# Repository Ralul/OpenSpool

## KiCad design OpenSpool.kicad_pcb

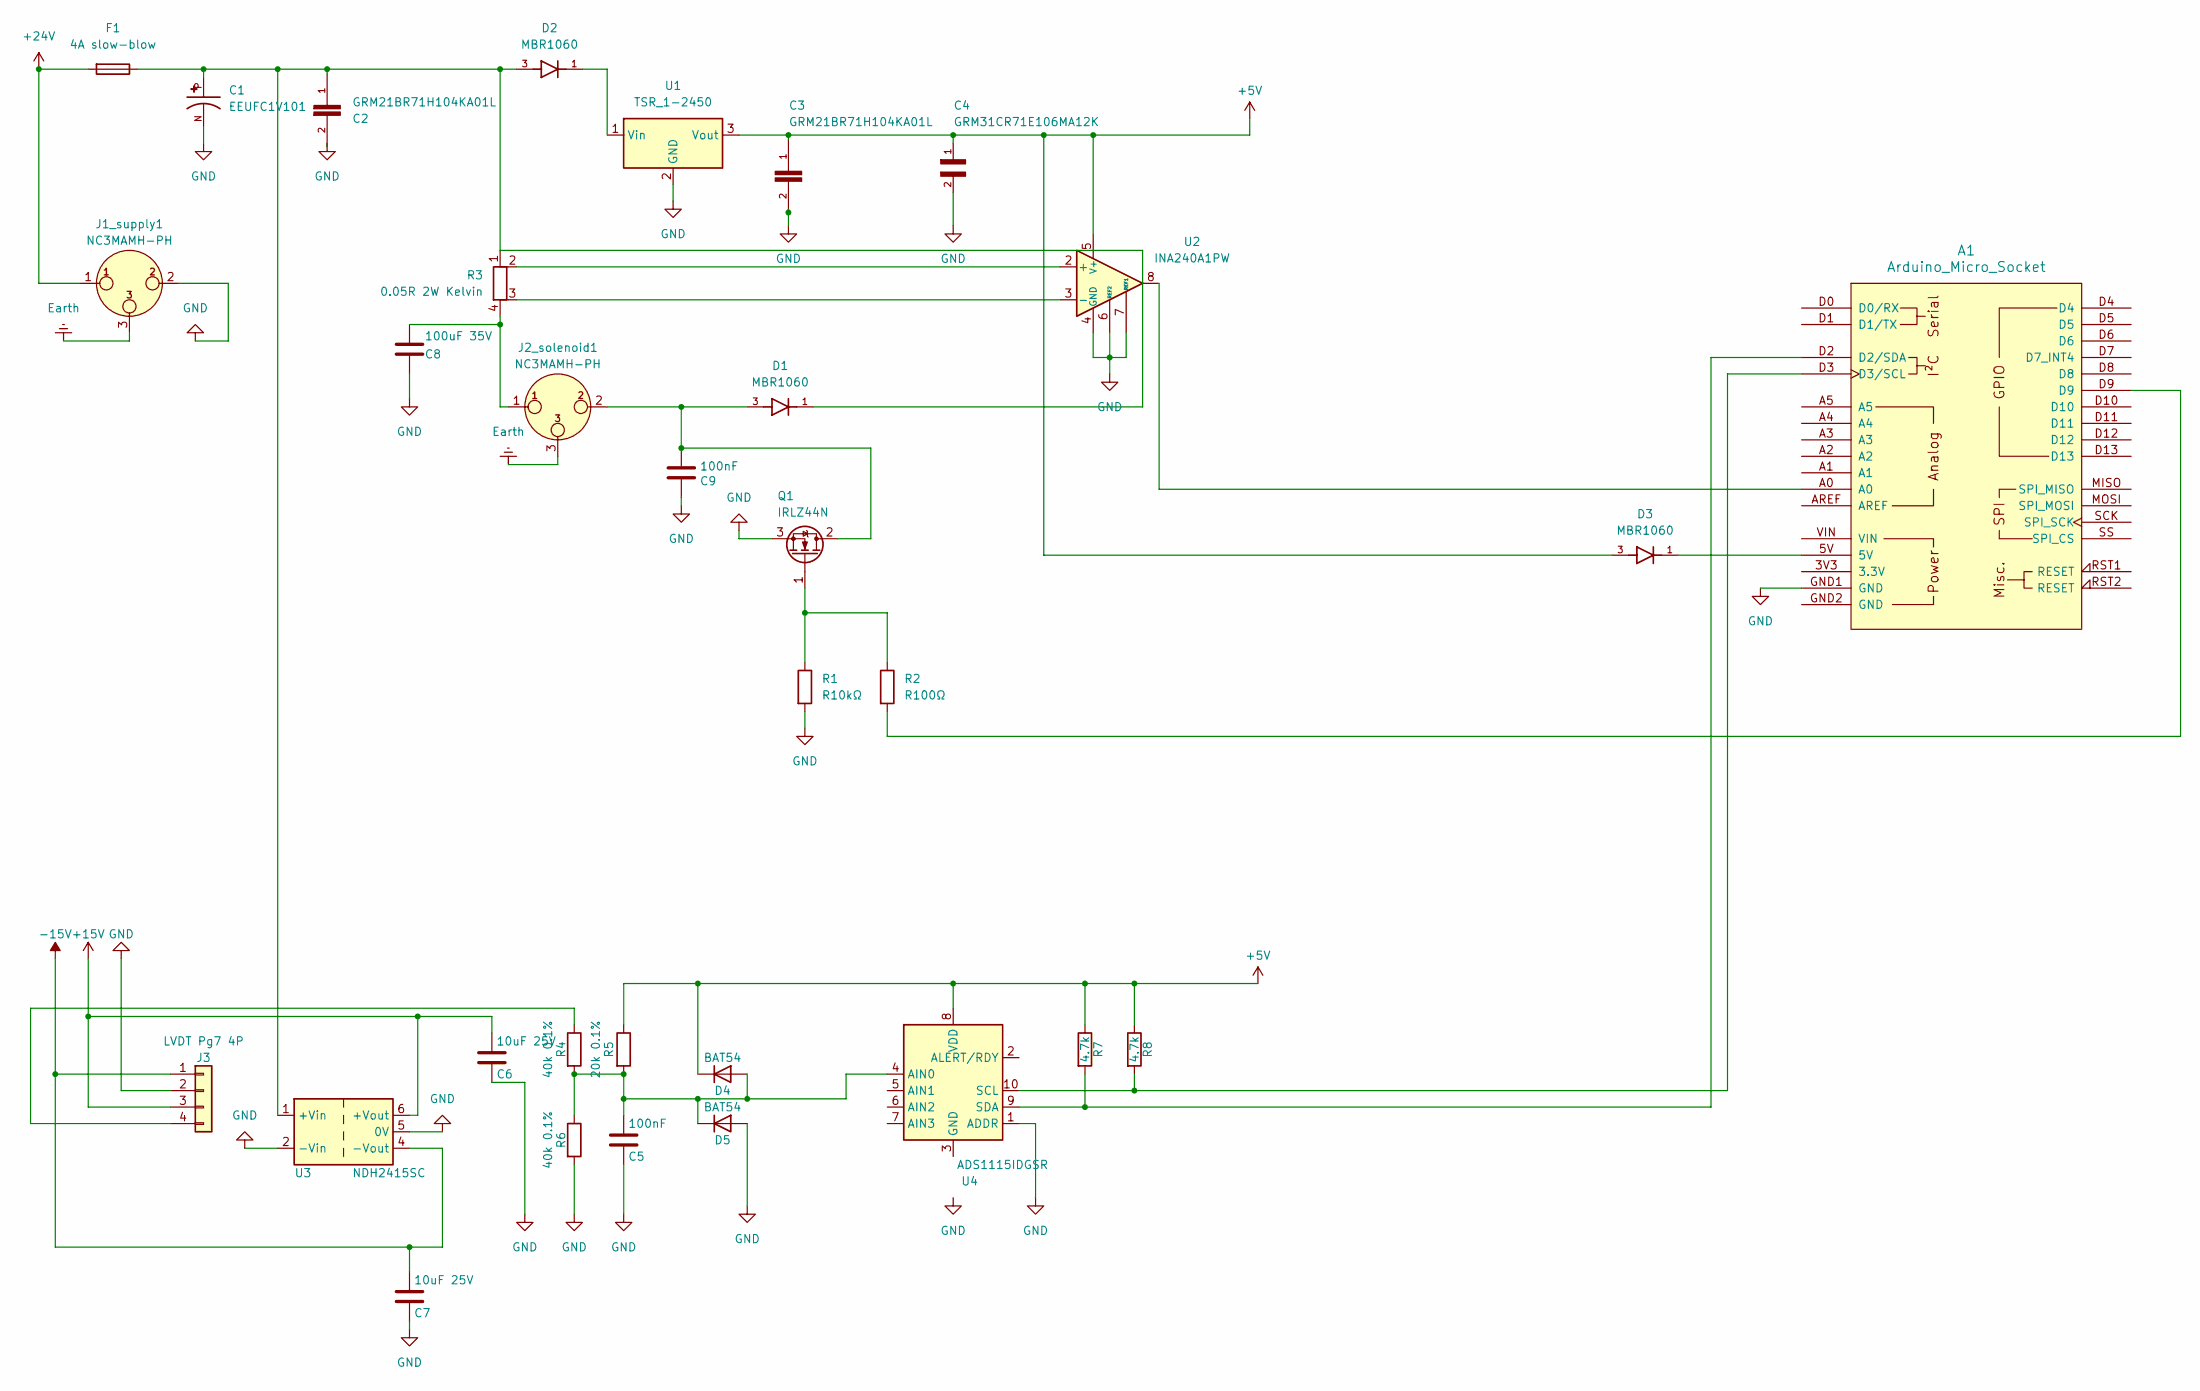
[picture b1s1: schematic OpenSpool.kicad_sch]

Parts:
A1: Arduino_Micro_Socket
C1: EEUFC1V101; CAPPRD350W60D800H1150; MPN EEU-FC1V101
C2, C3: GRM21BR71H104KA01L; CAPC2012X135; MPN GRM21BR71H104KA01L
C4: GRM31CR71E106MA12K; CAPC3216X180N; MPN GRM31CR71E106MA12K
C5, C9: 100nF; C_0805_2012Metric
C6, C7: 10uF 25V; CP_Elec_6.3x7.7
C8: 100uF 35V; CP_Elec_10x10
D1, D2, D3: MBR1060; TO508P1050X476X2020-2; MPN MBR1060
D4, D5: BAT54; SOT-23
F1: 4A slow-blow; Fuseholder_Clip-5x20mm_Littelfuse_111_Inline_P20.00x5.00mm_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; MPN Littelfuse 0217004.HXP
J1_supply1, J2_solenoid1: NC3MAMH-PH; Jack_XLR_Neutrik_NC3MAMH-PH_Horizontal
J3: LVDT Pg7 4P; PinSocket_1x04_P2.54mm_Vertical
Q1: IRLZ44N; TO-220-3_Vertical
R1: R10kΩ; R_0805_2012Metric
R2: R100Ω; R_0805_2012Metric
R3: 0.05R 2W Kelvin; R_Shunt_4W; Tolerance 1%; MPN 4-terminal shunt 50mohm 2W (e.g. Isabel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
R4, R6: 40k 0.1%; R_0805_2012Metric
R5: 20k 0.1%; R_0805_2012Metric
R7, R8: 4.7k; R_0805_2012Metric
U1: TSR_1-2450; Converter_DCDC_TRACO_TSR-1_THT
U2: INA240A1PW; TSSOP-8_4.4x3mm_P0.65mm
U3: NDH2415SC; Converter_DCDC_XP_POWER-IHxxxxS_THT; MPN NDH2415SC
U4: ADS1115IDGSR; TSSOP-10_3x3mm_P0.5mm; MPN ADS1115IDGSR; LCSC C7425545

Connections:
+5V: C3.1, C4.1, D3.3, D4.1 (K), R5.1, R7.1, R8.1, U1.3 (Vout), U2.5 (V+), U4.8 (VDD)
+15V: C6.1, J3.3, U3.6 (+Vout)
+24V: F1.2, J1_supply1.1
-15V: C7.1, J3.1, U3.4 (-Vout)
Earth: J1_supply1.3, J2_solenoid1.3
GND: A1.GND1 (GND), C1.N, C2.2, C3.2, C4.2, C5.2, C6.2, C7.2, C8.2, C9.2, D5.2 (A), J1_supply1.2, J3.2, Q1.3 (S), R1.2, R6.2, U1.2 (GND), U2.1 (GND), U2.4 (GND), U2.6 (REF2), U2.7 (REF1), U3.2 (-Vin), U3.5 (0V), U4.1 (ADDR)
unnamed: A1.D2 (D2/SDA), R7.2, U4.9 (SDA)
unnamed: A1.D3 (D3/SCL), R8.2, U4.10 (SCL)
unnamed: A1.5V, D3.1
unnamed: A1.A0, U2.8
unnamed: A1.D9, R2.2
unnamed: C8.1, J2_solenoid1.1, R3.4
unnamed: C5.1, D4.2 (A), D5.1 (K), R4.2, R5.2, R6.1, U4.4 (AIN0)
unnamed: J3.4, R4.1
unnamed: C9.1, D1.3, J2_solenoid1.2, Q1.2 (D)
unnamed: Q1.1 (G), R1.1, R2.1
unnamed: D2.1, U1.1 (Vin)
unnamed: R3.2, U2.2 (+)
unnamed: R3.3, U2.3 (-)
unnamed: C1.P, C2.1, D1.1, D2.3, F1.1, R3.1, U3.1 (+Vin)

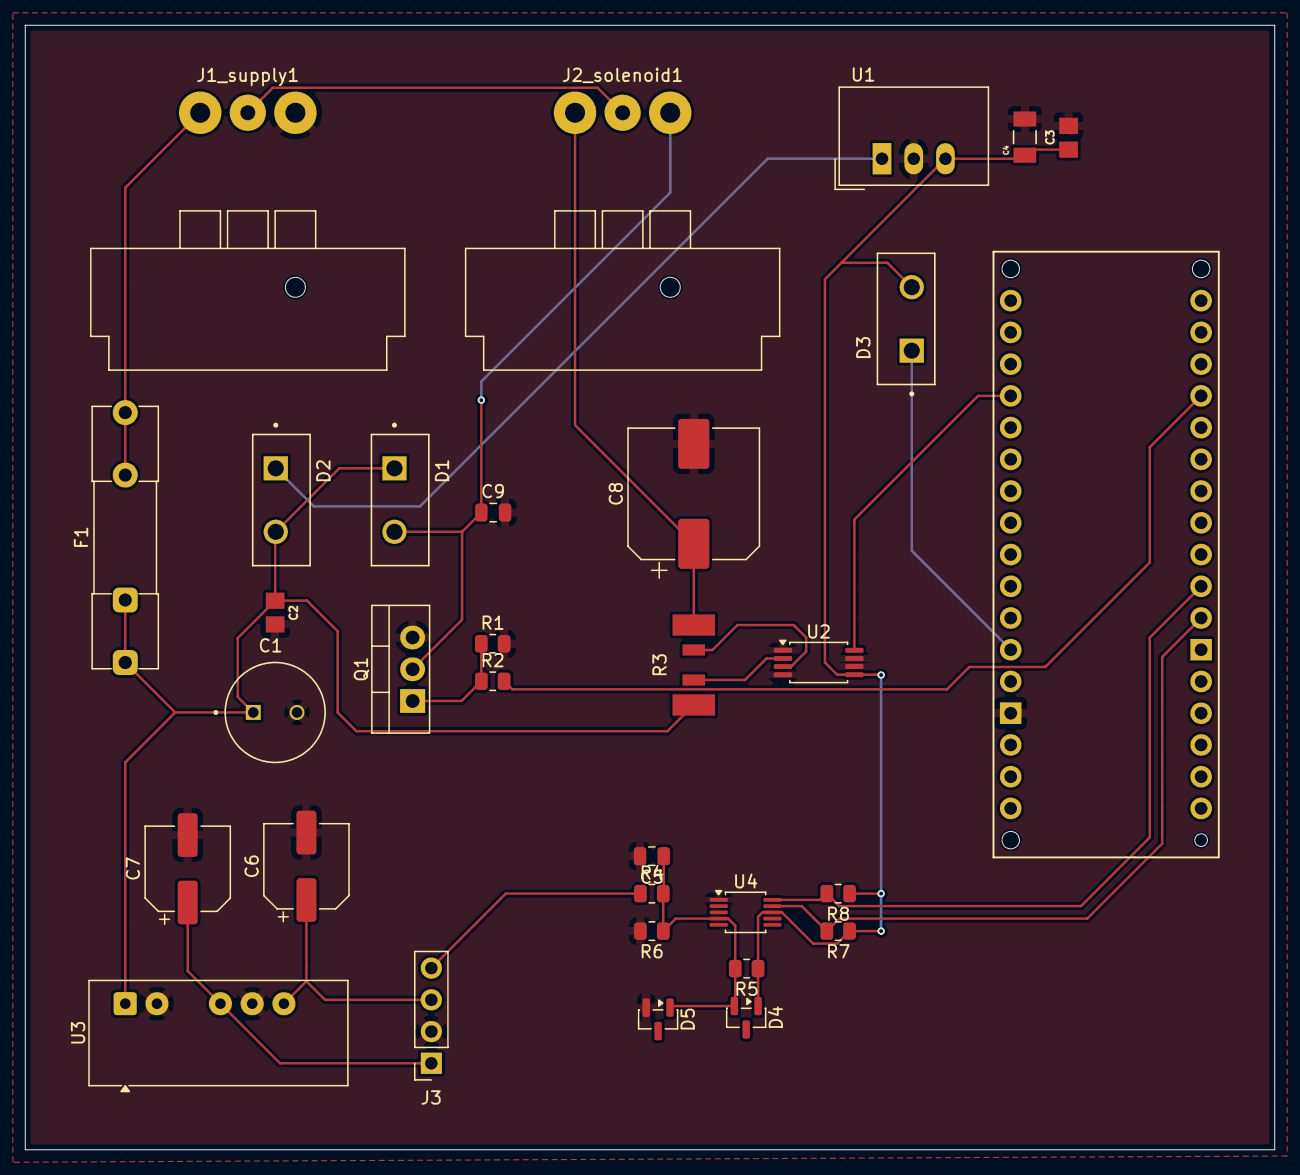
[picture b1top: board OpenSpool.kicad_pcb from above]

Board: 2 copper layers, 100.0 x 90.0 mm, 32 parts (0 on the bottom side), 20 nets.
